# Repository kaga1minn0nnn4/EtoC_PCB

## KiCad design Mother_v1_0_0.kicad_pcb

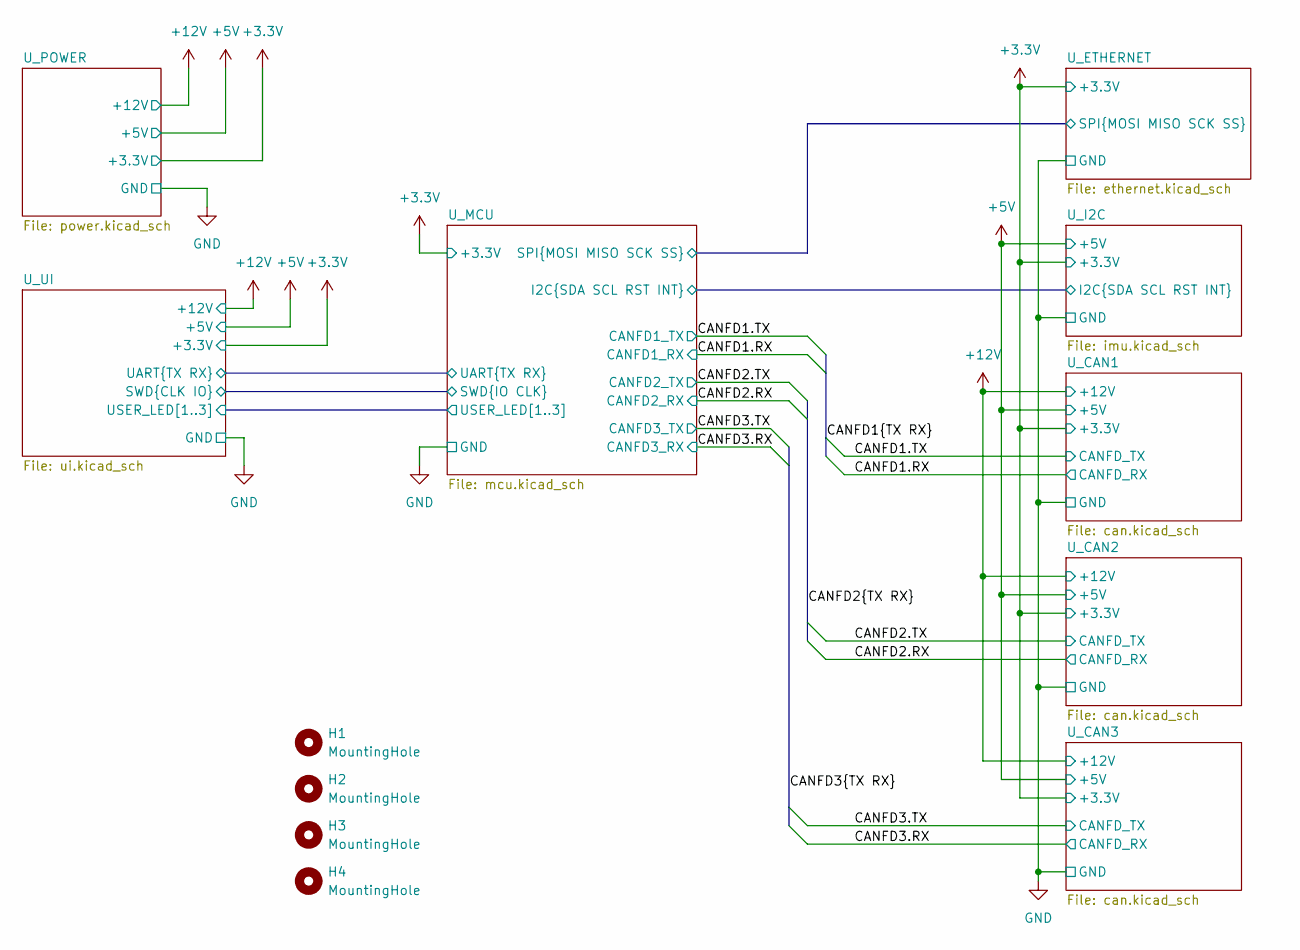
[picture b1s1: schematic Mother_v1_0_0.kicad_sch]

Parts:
H1, H2, H3, H4: MountingHole; MountingHole_3.2mm_M3

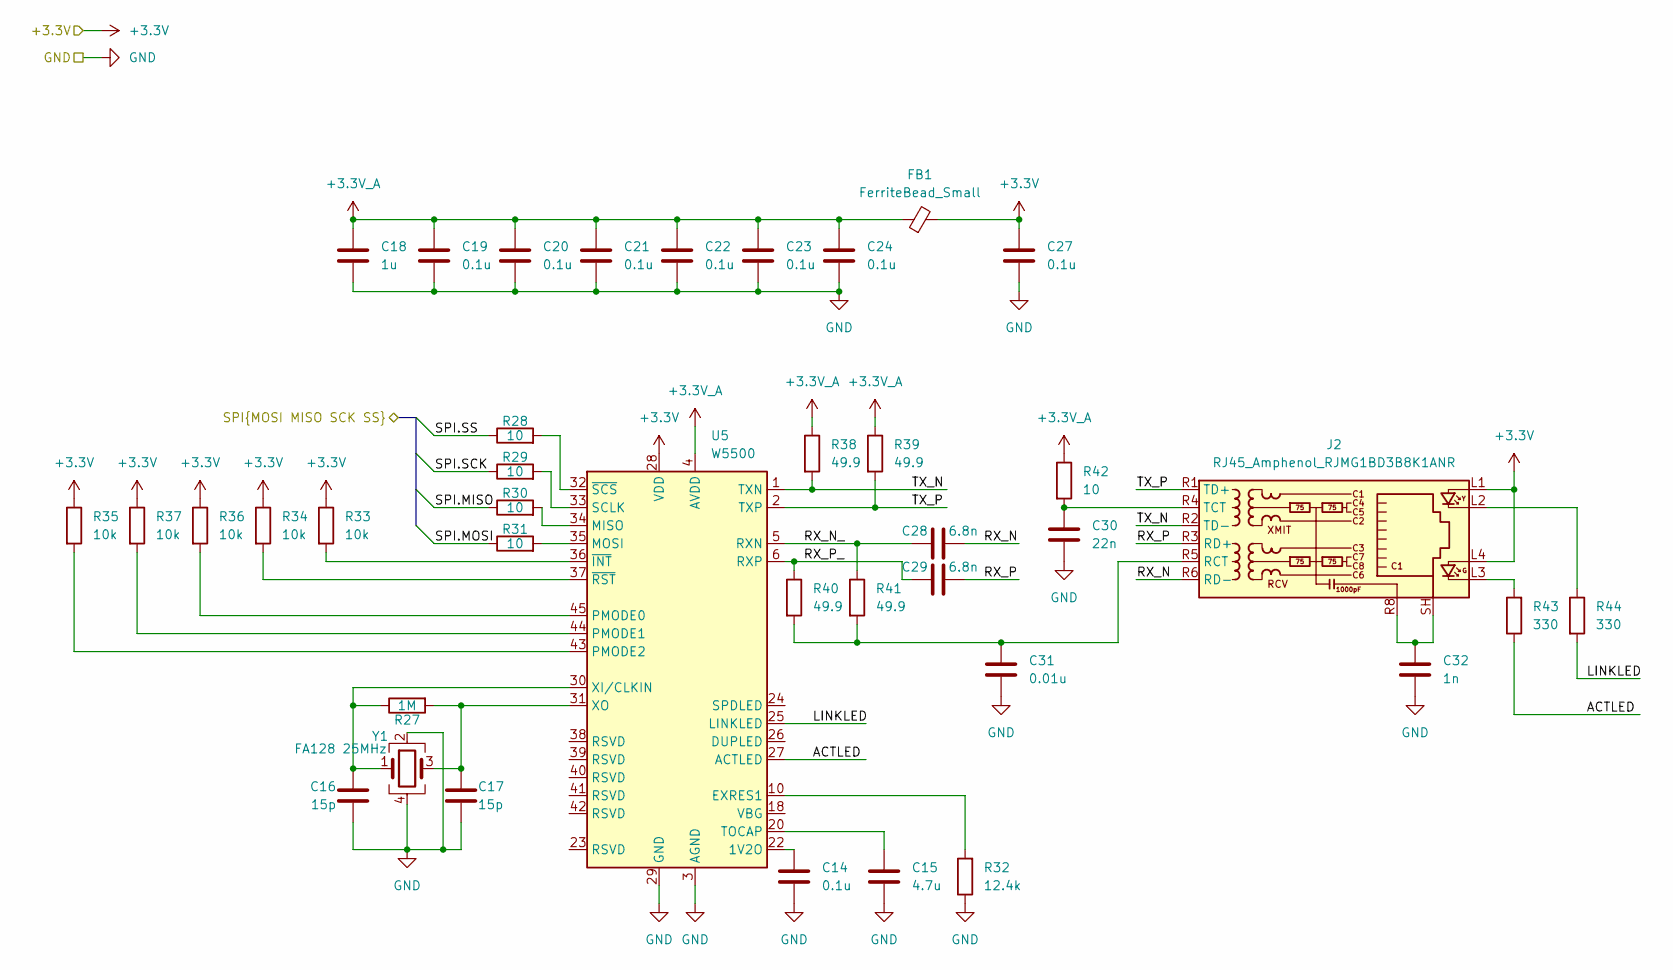
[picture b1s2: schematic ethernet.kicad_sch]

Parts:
C14, C19, C20, C21, C22, C23, C24, C27: 0.1u; C_0402_1005Metric
C15: 4.7u; C_0402_1005Metric
C16, C17: 15p; C_0402_1005Metric
C18: 1u; C_0402_1005Metric
C28, C29: 6.8n; C_0402_1005Metric
C30: 22n; C_0402_1005Metric
C31: 0.01u; C_0402_1005Metric
C32: 1n; C_0402_1005Metric
FB1: FerriteBead_Small; L_0603_1608Metric
J2: RJ45_Amphenol_RJMG1BD3B8K1ANR
R27: 1M; R_0402_1005Metric
R28, R29, R30, R31, R42: 10; R_0402_1005Metric
R32: 12.4k; R_0402_1005Metric
R33, R34, R35, R36, R37: 10k; R_0402_1005Metric
R38, R39, R40, R41: 49.9; R_0402_1005Metric
R43, R44: 330; R_0402_1005Metric
U5: W5500; LQFP-48_7x7mm_P0.5mm
Y1: FA128 25MHz; Crystal_SMD_SeikoEpson_FA128-4Pin_2.0x1.6mm

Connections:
+3.3V: C27.1, FB1.2, J2.L1, J2.L4, R33.1, R34.1, R35.1, R36.1, R37.1, U5.28 (VDD); also elsewhere on the board
+3.3V_A: C18.1, C19.1, C20.1, C21.1, C22.1, C23.1, C24.1, FB1.1, R38.1, R39.1, R42.1, U5.4 (AVDD), U5.8 (AVDD), U5.11 (AVDD), U5.15 (AVDD), U5.17 (AVDD), U5.21 (AVDD)
/U_ETHERNET/ACTLED: R43.1, U5.27 (ACTLED)
/U_ETHERNET/LINKLED: R44.2, U5.25 (LINKLED)
/U_ETHERNET/RX_N: C28.2, J2.R6 (RD-)
/U_ETHERNET/RX_N_: C28.1, R41.1, U5.5 (RXN)
/U_ETHERNET/RX_P: C29.2, J2.R3 (RD+)
/U_ETHERNET/RX_P_: C29.1, R40.1, U5.6 (RXP)
/U_ETHERNET/SPI.MISO: R30.1; also elsewhere on the board
/U_ETHERNET/SPI.MOSI: R31.1; also elsewhere on the board
/U_ETHERNET/SPI.SCK: R29.1; also elsewhere on the board
/U_ETHERNET/SPI.SS: R28.1; also elsewhere on the board
/U_ETHERNET/TX_N: J2.R2 (TD-), R38.2, U5.1 (TXN)
/U_ETHERNET/TX_P: J2.R1 (TD+), R39.2, U5.2 (TXP)
GND: C14.2, C15.2, C16.2, C17.2, C18.2, C19.2, C20.2, C21.2, C22.2, C23.2, C24.2, C27.2, C30.2, C31.2, C32.2, R32.1, U5.3 (AGND), U5.9 (AGND), U5.14 (AGND), U5.16 (AGND), U5.19 (AGND), U5.29 (GND), U5.48 (AGND), Y1.2, Y1.4; also elsewhere on the board
unnamed: C32.1, J2.R8, J2.SH
unnamed: J2.L2, R44.1
unnamed: J2.L3, R43.2
unnamed: C31.1, J2.R5 (RCT), R40.2, R41.2
unnamed: C30.1, J2.R4 (TCT), R42.2
unnamed: C14.1, U5.22 (1V2O)
unnamed: R32.2, U5.10 (EXRES1)
unnamed: R30.2, U5.34 (MISO)
unnamed: R31.2, U5.35 (MOSI)
unnamed: R36.2, U5.45 (PMODE0)
unnamed: R37.2, U5.44 (PMODE1)
unnamed: R35.2, U5.43 (PMODE2)
unnamed: R29.2, U5.33 (SCLK)
unnamed: C15.1, U5.20 (TOCAP)
unnamed: C16.1, R27.1, U5.30 (XI/CLKIN), Y1.1
unnamed: C17.1, R27.2, U5.31 (XO), Y1.3
unnamed: R33.2, U5.36 (~INT)
unnamed: R34.2, U5.37 (~RST)
unnamed: R28.2, U5.32 (~SCS)

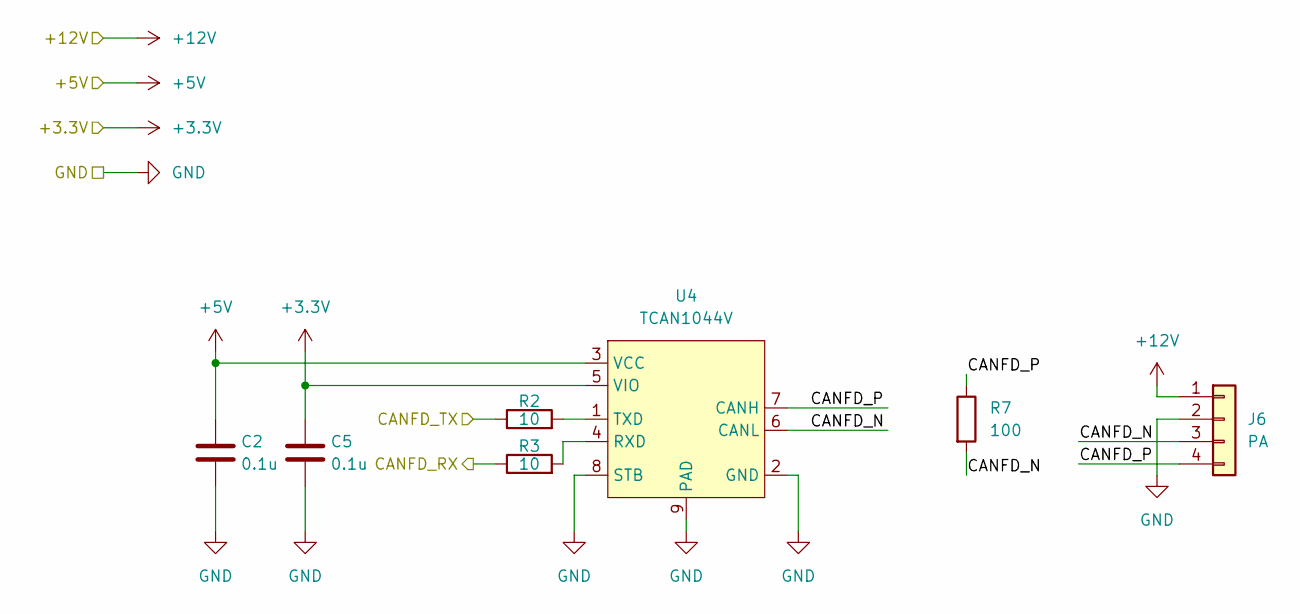
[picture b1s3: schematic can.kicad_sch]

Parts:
C2, C5: 0.1u; C_0402_1005Metric
J6: PA; S04B-PASK-2
R2, R3: 10; R_0402_1005Metric
R7: 100; R_0402_1005Metric
U4: TCAN1044V; VSON-8-1EP_3x3mm_P0.65mm_EP1.65x2.4mm

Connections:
+3.3V: C5.1, U4.5 (VIO); also elsewhere on the board
+5V: C2.1, U4.3 (VCC); also elsewhere on the board
+12V: J6.1; also elsewhere on the board
/CANFD2.RX: R3.1; also elsewhere on the board
/CANFD2.TX: R2.1; also elsewhere on the board
/U_CAN2/CANFD_N: J6.3, R7.2, U4.6 (CANL)
/U_CAN2/CANFD_P: J6.4, R7.1, U4.7 (CANH)
GND: C2.2, C5.2, J6.2, U4.2 (GND), U4.8 (STB), U4.9 (PAD); also elsewhere on the board
unnamed: R3.2, U4.4 (RXD)
unnamed: R2.2, U4.1 (TXD)

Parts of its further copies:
C3, C4, C6, C43: 0.1u; C_0402_1005Metric
J5, J8: PA; S04B-PASK-2
R4, R5, R8, R9: 10; R_0402_1005Metric
R6, R50: 100; R_0402_1005Metric
U7, U8: TCAN1044V; VSON-8-1EP_3x3mm_P0.65mm_EP1.65x2.4mm

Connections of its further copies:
+3.3V: C4.1, C43.1, U7.5 (VIO), U8.5 (VIO); also elsewhere on the board
+5V: C3.1, C6.1, U7.3 (VCC), U8.3 (VCC); also elsewhere on the board
+12V: J5.1, J8.1; also elsewhere on the board
/CANFD1.RX: R5.1; also elsewhere on the board
/CANFD1.TX: R4.1; also elsewhere on the board
/CANFD3.RX: R9.1; also elsewhere on the board
/CANFD3.TX: R8.1; also elsewhere on the board
/U_CAN1/CANFD_N: J5.3, R6.2, U7.6 (CANL)
/U_CAN1/CANFD_P: J5.4, R6.1, U7.7 (CANH)
/U_CAN3/CANFD_N: J8.3, R50.2, U8.6 (CANL)
/U_CAN3/CANFD_P: J8.4, R50.1, U8.7 (CANH)
GND: C3.2, C4.2, C6.2, C43.2, J5.2, J8.2, U7.2 (GND), U7.8 (STB), U7.9 (PAD), U8.2 (GND), U8.8 (STB), U8.9 (PAD); also elsewhere on the board
unnamed: R5.2, U7.4 (RXD)
unnamed: R4.2, U7.1 (TXD)
unnamed: R9.2, U8.4 (RXD)
unnamed: R8.2, U8.1 (TXD)

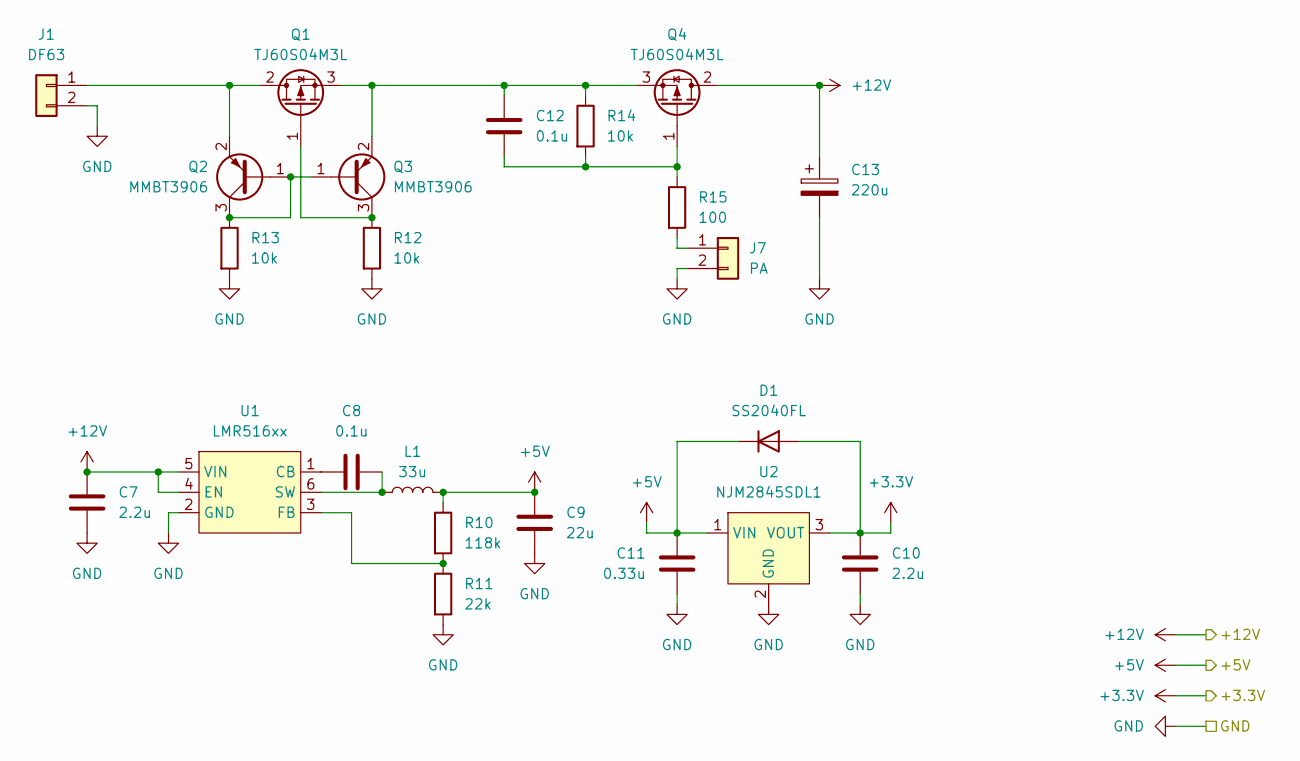
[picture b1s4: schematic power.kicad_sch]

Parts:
C7: 2.2u; C_0603_1608Metric
C8: 0.1u; C_0402_1005Metric
C9: 22u; C_0805_2012Metric
C10: 2.2u; C_0603_1608Metric_Pad1.08x0.95mm_HandSolder
C11: 0.33u; C_0603_1608Metric_Pad1.08x0.95mm_HandSolder
C12: 0.1u; C_0603_1608Metric_Pad1.08x0.95mm_HandSolder
C13: 220u; CP_Radial_D8.0mm_P3.50mm
D1: SS2040FL; Nexperia_CFP3_SOD-123W
J1: DF63; DF63M-2P-3.96DS
J7: PA; S02B-PASK-2
L1: 33u; L_APV_ANR5040
Q1, Q4: TJ60S04M3L; TO-252-2
Q2, Q3: MMBT3906; SOT-23
R10: 118k; R_0402_1005Metric
R11: 22k; R_0402_1005Metric
R12, R13: 10k; R_0402_1005Metric
R14: 10k; R_0603_1608Metric_Pad0.98x0.95mm_HandSolder
R15: 100; R_0603_1608Metric_Pad0.98x0.95mm_HandSolder
U1: LMR516xx; SOT-23-6
U2: NJM2845SDL1; TO-252-2

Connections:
+3.3V: C10.2, D1.2 (A), U2.3 (VOUT); also elsewhere on the board
+5V: C9.1, C11.2, D1.1 (K), L1.2, R10.1, U2.1 (VIN); also elsewhere on the board
+12V: C7.1, C13.1, Q4.2 (D), U1.4 (EN), U1.5 (VIN); also elsewhere on the board
GND: C7.2, C9.2, C10.1, C11.1, C13.2, J1.2, J7.2, R11.2, R12.2, R13.2, U1.2 (GND), U2.2 (GND); also elsewhere on the board
unnamed: J1.1, Q1.2 (D), Q2.2 (E)
unnamed: J7.1, R15.2
unnamed: Q1.1 (G), Q3.3 (C), R12.1
unnamed: C12.2, Q1.3 (S), Q3.2 (E), Q4.3 (S), R14.1
unnamed: Q2.1 (B), Q2.3 (C), Q3.1 (B), R13.1
unnamed: C12.1, Q4.1 (G), R14.2, R15.1
unnamed: C8.1, U1.1 (CB)
unnamed: R10.2, R11.1, U1.3 (FB)
unnamed: C8.2, L1.1, U1.6 (SW)

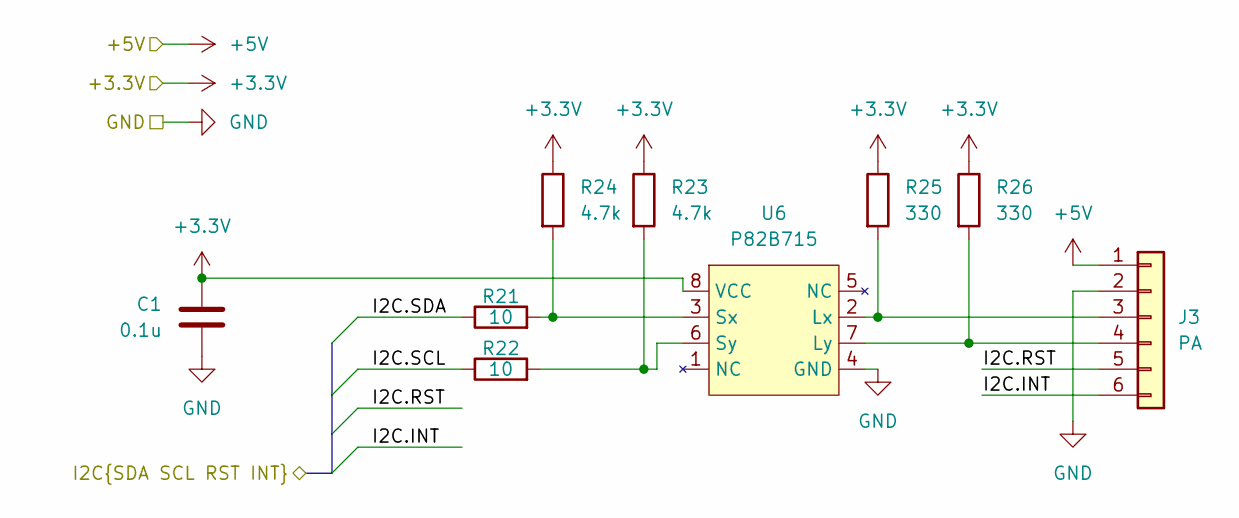
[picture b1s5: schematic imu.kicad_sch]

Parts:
C1: 0.1u; C_0402_1005Metric
J3: PA; S06B-PASK-2
R21, R22: 10; R_0402_1005Metric
R23, R24: 4.7k; R_0402_1005Metric
R25, R26: 330; R_0402_1005Metric
U6: P82B715; SOIC-8_3.9x4.9mm_P1.27mm

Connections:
+3.3V: C1.1, R23.1, R24.1, R25.1, R26.1, U6.8 (VCC); also elsewhere on the board
+5V: J3.1; also elsewhere on the board
/U_I2C/I2C.INT: J3.6; also elsewhere on the board
/U_I2C/I2C.RST: J3.5; also elsewhere on the board
/U_I2C/I2C.SCL: R22.1; also elsewhere on the board
/U_I2C/I2C.SDA: R21.1; also elsewhere on the board
GND: C1.2, J3.2, U6.4 (GND); also elsewhere on the board
unnamed: J3.3, R25.2, U6.2 (Lx)
unnamed: J3.4, R26.2, U6.7 (Ly)
unnamed: R21.2, R24.2, U6.3 (Sx)
unnamed: R22.2, R23.2, U6.6 (Sy)

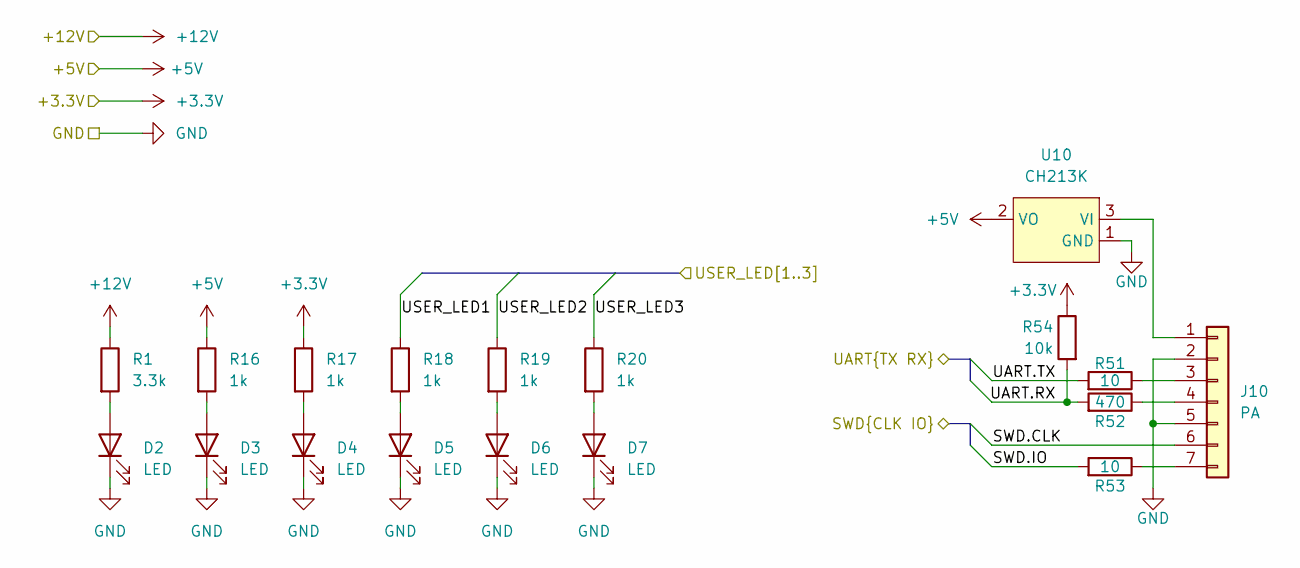
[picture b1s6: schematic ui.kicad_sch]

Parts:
D2, D3, D4, D5, D6, D7: LED; LED_0603_1608Metric_Pad1.05x0.95mm_HandSolder
J10: PA; S07B-PASK-2
R1: 3.3k; R_0402_1005Metric
R16, R17, R18, R19, R20: 1k; R_0402_1005Metric
R51, R53: 10; R_0402_1005Metric
R52: 470; R_0402_1005Metric
R54: 10k; R_0402_1005Metric
U10: CH213K; SOT-23-3

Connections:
+3.3V: R17.1, R54.1; also elsewhere on the board
+5V: R16.1, U10.2 (VO); also elsewhere on the board
+12V: R1.1; also elsewhere on the board
/U_MCU/SWD.CLK: J10.6; also elsewhere on the board
/U_MCU/SWD.IO: R53.2; also elsewhere on the board
/U_MCU/UART.RX: R52.2, R54.2; also elsewhere on the board
/U_MCU/UART.TX: R51.2; also elsewhere on the board
/U_MCU/USER_LED1: R18.1; also elsewhere on the board
/U_MCU/USER_LED2: R19.1; also elsewhere on the board
/U_MCU/USER_LED3: R20.1; also elsewhere on the board
GND: D2.1 (K), D3.1 (K), D4.1 (K), D5.1 (K), D6.1 (K), D7.1 (K), J10.2, J10.5, U10.1 (GND); also elsewhere on the board
unnamed: D2.2 (A), R1.2
unnamed: D3.2 (A), R16.2
unnamed: D4.2 (A), R17.2
unnamed: D5.2 (A), R18.2
unnamed: D6.2 (A), R19.2
unnamed: D7.2 (A), R20.2
unnamed: J10.1, U10.3 (VI)
unnamed: J10.3, R51.1
unnamed: J10.4, R52.1
unnamed: J10.7, R53.1

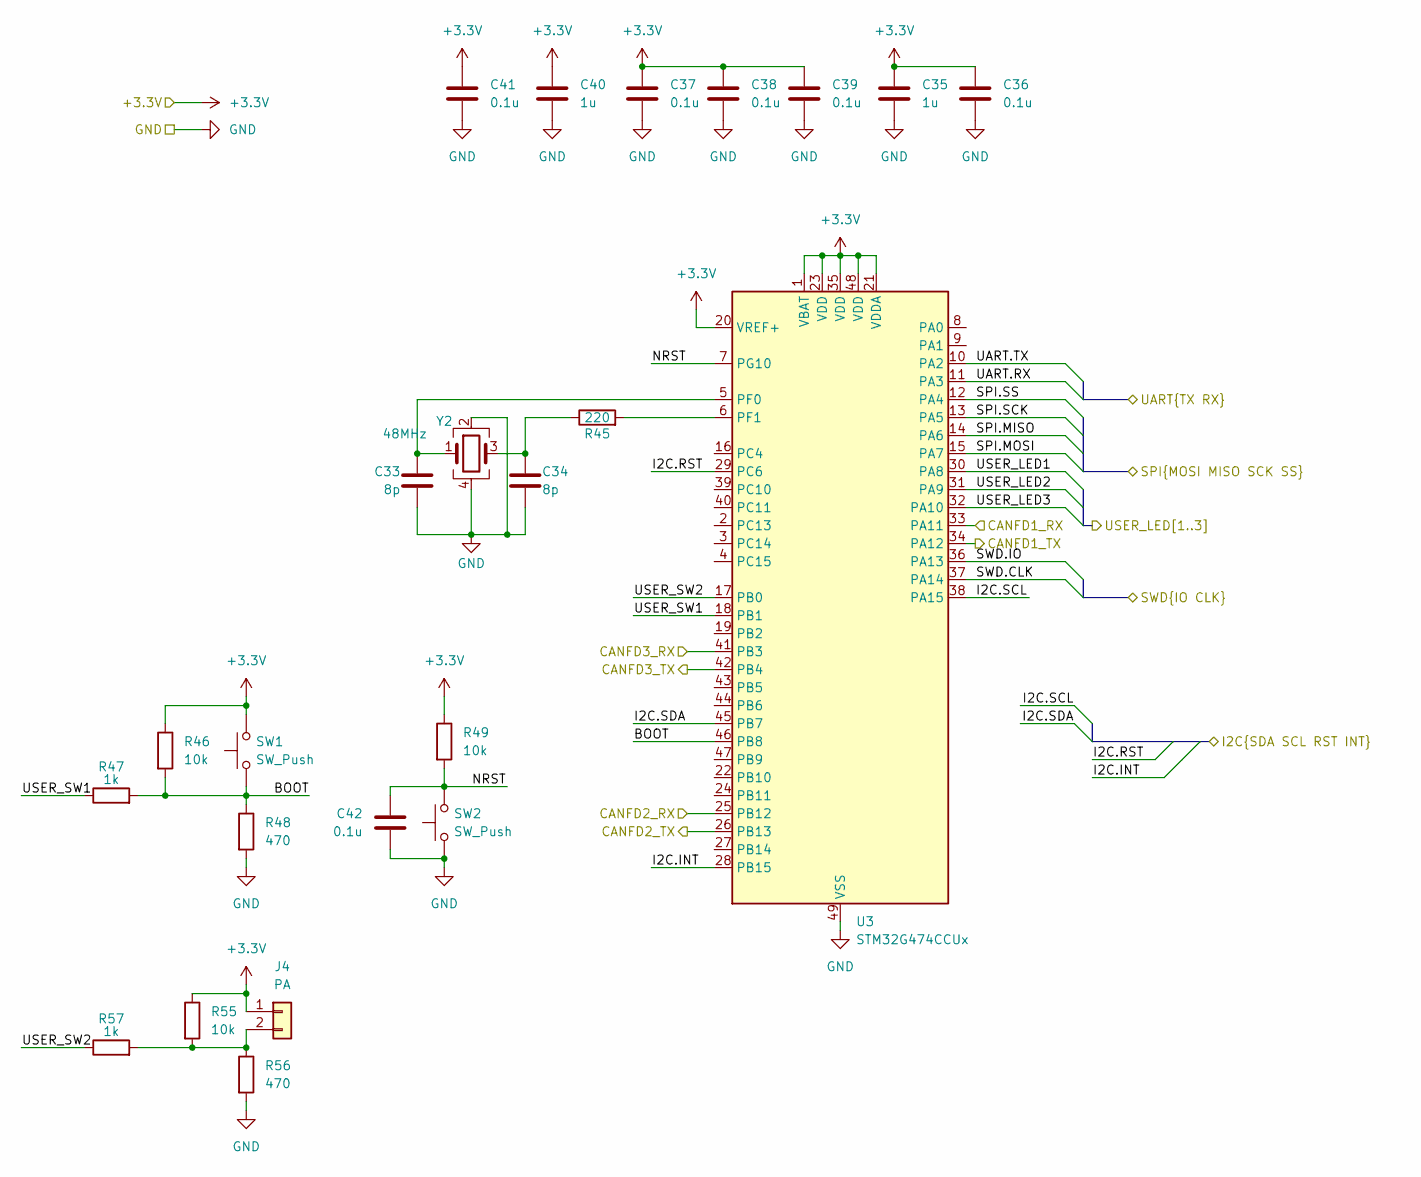
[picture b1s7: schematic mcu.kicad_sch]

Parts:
C33, C34: 8p; C_0402_1005Metric
C35, C40: 1u; C_0402_1005Metric
C36, C37, C38, C39, C41, C42: 0.1u; C_0402_1005Metric
J4: PA; S02B-PASK-2
R45: 220; R_0402_1005Metric
R46, R49, R55: 10k; R_0402_1005Metric
R47, R57: 1k; R_0402_1005Metric
R48, R56: 470; R_0402_1005Metric
SW1, SW2: SW_Push; TVAF06-A020B-R
U3: STM32G474CCUx; QFN-48-1EP_7x7mm_P0.5mm_EP5.6x5.6mm
Y2: 48MHz; Crystal_SMD_SeikoEpson_FA128-4Pin_2.0x1.6mm

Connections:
+3.3V: C35.1, C36.1, C37.1, C38.1, C39.1, C40.1, C41.1, J4.1, R46.1, R49.1, R55.1, SW1.2, U3.1 (VBAT), U3.20 (VREF+), U3.21 (VDDA), U3.23 (VDD), U3.35 (VDD), U3.48 (VDD); also elsewhere on the board
/CANFD1.RX: U3.33 (PA11); also elsewhere on the board
/CANFD1.TX: U3.34 (PA12); also elsewhere on the board
/CANFD2.RX: U3.25 (PB12); also elsewhere on the board
/CANFD2.TX: U3.26 (PB13); also elsewhere on the board
/CANFD3.RX: U3.41 (PB3); also elsewhere on the board
/CANFD3.TX: U3.42 (PB4); also elsewhere on the board
/U_ETHERNET/SPI.MISO: U3.14 (PA6); also elsewhere on the board
/U_ETHERNET/SPI.MOSI: U3.15 (PA7); also elsewhere on the board
/U_ETHERNET/SPI.SCK: U3.13 (PA5); also elsewhere on the board
/U_ETHERNET/SPI.SS: U3.12 (PA4); also elsewhere on the board
/U_I2C/I2C.INT: U3.28 (PB15); also elsewhere on the board
/U_I2C/I2C.RST: U3.29 (PC6); also elsewhere on the board
/U_I2C/I2C.SCL: U3.38 (PA15); also elsewhere on the board
/U_I2C/I2C.SDA: U3.45 (PB7); also elsewhere on the board
/U_MCU/BOOT: R46.2, R47.2, R48.1, SW1.1, U3.46 (PB8)
/U_MCU/NRST: C42.1, R49.2, SW2.2, U3.7 (PG10)
/U_MCU/SWD.CLK: U3.37 (PA14); also elsewhere on the board
/U_MCU/SWD.IO: U3.36 (PA13); also elsewhere on the board
/U_MCU/UART.RX: U3.11 (PA3); also elsewhere on the board
/U_MCU/UART.TX: U3.10 (PA2); also elsewhere on the board
/U_MCU/USER_LED1: U3.30 (PA8); also elsewhere on the board
/U_MCU/USER_LED2: U3.31 (PA9); also elsewhere on the board
/U_MCU/USER_LED3: U3.32 (PA10); also elsewhere on the board
/U_MCU/USER_SW1: R47.1, U3.18 (PB1)
/U_MCU/USER_SW2: R57.1, U3.17 (PB0)
GND: C33.2, C34.2, C35.2, C36.2, C37.2, C38.2, C39.2, C40.2, C41.2, C42.2, R48.2, R56.2, SW2.1, U3.49 (VSS), Y2.2, Y2.4; also elsewhere on the board
unnamed: C34.1, R45.1, Y2.3
unnamed: J4.2, R55.2, R56.1, R57.2
unnamed: C33.1, U3.5 (PF0), Y2.1
unnamed: R45.2, U3.6 (PF1)

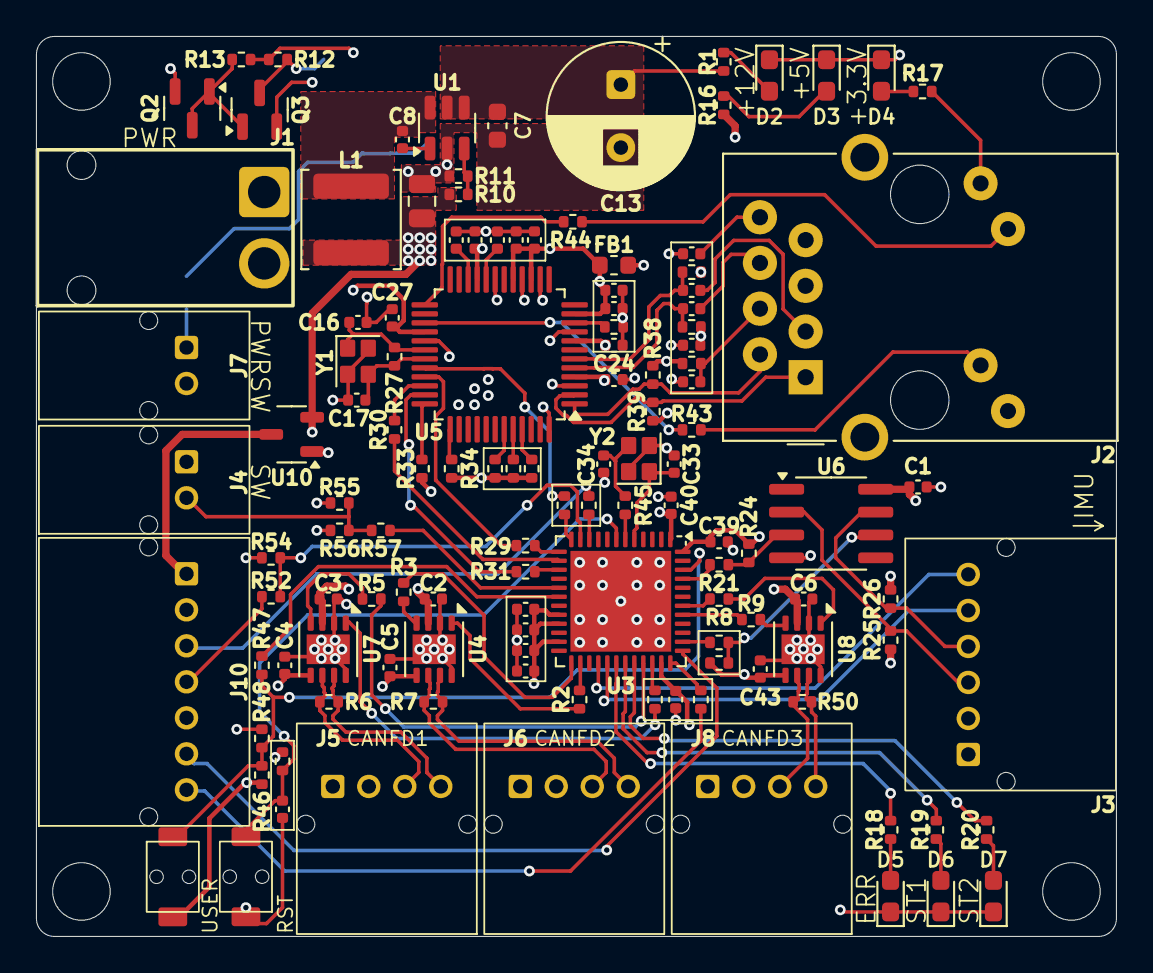
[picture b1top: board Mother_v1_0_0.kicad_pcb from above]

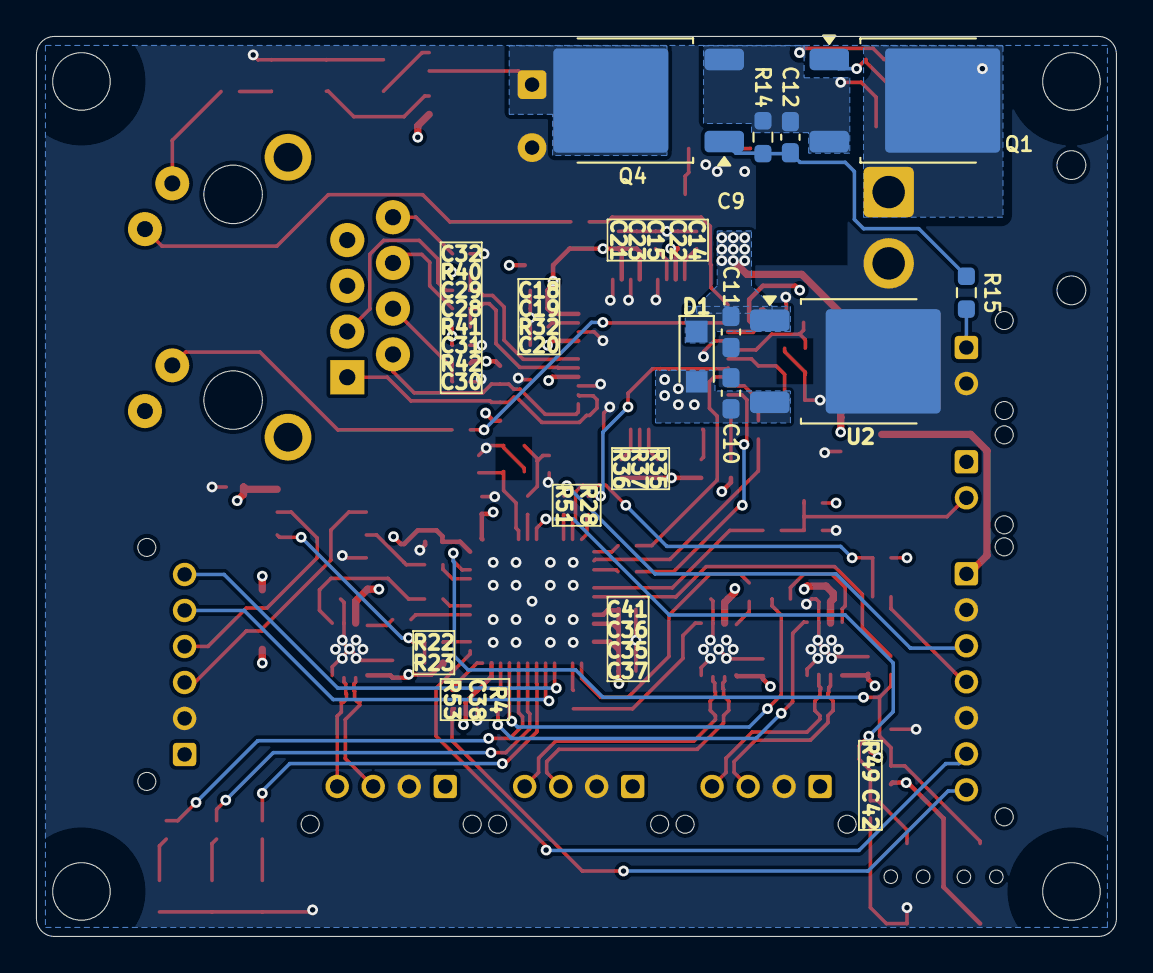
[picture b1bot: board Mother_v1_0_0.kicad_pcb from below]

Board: 4 copper layers, 60.0 x 50.0 mm, 137 parts (9 on the bottom side), 96 nets.

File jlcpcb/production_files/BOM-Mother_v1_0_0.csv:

Comment,Designator,Footprint,LCSC,Quantity
1k,"R16,R17,R18,R19,R20,R47,R57",R_0402_1005Metric,C11702,7
STM32G474CCUx,U3,QFN-48-1EP_7x7mm_P0.5mm_EP5.6x5.6mm,C1341847,1
0.01u,C31,C_0402_1005Metric,C15195,1
1n,C32,C_0402_1005Metric,C1523,1
0.1u,"C1,C14,C19,C2,C20,C21,C22,C23,C24,C27,C3,C36,C37,C38,C39,C4,C41,C42,C43,C5,C6,C8",C_0402_1005Metric,C1525,22
22n,C30,C_0402_1005Metric,C1532,1
6.8n,"C28,C29",C_0402_1005Metric,C1542,2
15p,"C16,C17",C_0402_1005Metric,C1548,2
8p,"C33,C34",C_0402_1005Metric,C1549,2
LMR516xx,U1,SOT-23-6,C22428253,1
2.2u,C7,C_0603_1608Metric,C23630,1
4.7u,C15,C_0402_1005Metric,C23733,1
100,"R50,R6,R7",R_0402_1005Metric,C25076,3
10,"R2,R21,R22,R28,R29,R3,R30,R31,R4,R42,R5,R51,R53,R8,R9",R_0402_1005Metric,C25077,15
220,R45,R_0402_1005Metric,C25091,1
330,"R25,R26,R43,R44",R_0402_1005Metric,C25104,4
470,"R48,R52,R56",R_0402_1005Metric,C25117,3
49.9,"R38,R39,R40,R41",R_0402_1005Metric,C25120,4
48MHz,Y2,Crystal_SMD_SeikoEpson_FA128-4Pin_2.0x1.6mm,C255900,1
10k,"R12,R13,R33,R34,R35,R36,R37,R46,R49,R54,R55",R_0402_1005Metric,C25744,11
118k,R10,R_0402_1005Metric,C25748,1
12.4k,R32,R_0402_1005Metric,C25752,1
22k,R11,R_0402_1005Metric,C25768,1
3.3k,R1,R_0402_1005Metric,C25890,1
4.7k,"R23,R24",R_0402_1005Metric,C25900,2
1M,R27,R_0402_1005Metric,C26083,1
W5500,U5,LQFP-48_7x7mm_P0.5mm,C32843,1
FA128 25MHz,Y1,Crystal_SMD_SeikoEpson_FA128-4Pin_2.0x1.6mm,C37635328,1
22u,C9,C_0805_2012Metric,C45783,1
TCAN1044V,"U4,U7,U8",VSON-8-1EP_3x3mm_P0.65mm_EP1.65x2.4mm,C5215851,3
1u,"C18,C35,C40",C_0402_1005Metric,C52923,3
33u,L1,L_APV_ANR5040,C9390,1
LED,D6,LED_0603_1608Metric_Pad1.05x0.95mm_HandSolder,,1
SW_Push,SW1,TVAF06-A020B-R,,1
PA,J10,S07B-PASK-2,,1
SW_Push,SW2,TVAF06-A020B-R,,1
LED,D5,LED_0603_1608Metric_Pad1.05x0.95mm_HandSolder,,1
LED,D2,LED_0603_1608Metric_Pad1.05x0.95mm_HandSolder,,1
MMBT3906,Q2,SOT-23,,1
FerriteBead_Small,FB1,L_0603_1608Metric,,1
PA,J3,S06B-PASK-2,,1
CH213K,U10,SOT-23-3,,1
RJ45_Amphenol_RJMG1BD3B8K1ANR,J2,RJ45_Amphenol_RJMG1BD3B8K1ANR,,1
PA,J4,S02B-PASK-2,,1
LED,D4,LED_0603_1608Metric_Pad1.05x0.95mm_HandSolder,,1
LED,D3,LED_0603_1608Metric_Pad1.05x0.95mm_HandSolder,,1
PA,J6,S04B-PASK-2,,1
220u,C13,CP_Radial_D8.0mm_P3.50mm,,1
PA,J5,S04B-PASK-2,,1
P82B715,U6,SOIC-8_3.9x4.9mm_P1.27mm,,1
MMBT3906,Q3,SOT-23,,1
PA,J7,S02B-PASK-2,,1
LED,D7,LED_0603_1608Metric_Pad1.05x0.95mm_HandSolder,,1
DF63,J1,DF63M-2P-3.96DS,,1
PA,J8,S04B-PASK-2,,1
NJM2845SDL1,U2,TO-252-2,,1
SS2040FL,D1,Nexperia_CFP3_SOD-123W,,1
10k,R14,R_0603_1608Metric_Pad0.98x0.95mm_HandSolder,,1
TJ60S04M3L,Q1,TO-252-2,,1
0.33u,C11,C_0603_1608Metric_Pad1.08x0.95mm_HandSolder,,1
100,R15,R_0603_1608Metric_Pad0.98x0.95mm_HandSolder,,1
TJ60S04M3L,Q4,TO-252-2,,1
0.1u,C12,C_0603_1608Metric_Pad1.08x0.95mm_HandSolder,,1
2.2u,C10,C_0603_1608Metric_Pad1.08x0.95mm_HandSolder,,1

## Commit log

2026-02-26 Add project overview to README
